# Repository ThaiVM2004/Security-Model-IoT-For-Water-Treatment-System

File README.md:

# 🔒 Security Model IoT for Water Treatment System

A multi-layered IoT security system for real-time water treatment monitoring and control. The project integrates embedded sensors, a network firewall, cloud services, and a web dashboard with role-based access control (RBAC) to securely supervise water quality across collection and discharge tanks.

---

## 📋 Table of Contents

- [Overview](#overview)
- [System Architecture](#system-architecture)
- [Hardware Components](#hardware-components)
- [Software Stack](#software-stack)
- [Repository Structure](#repository-structure)
- [Getting Started](#getting-started)
  - [STM32 Firmware](#stm32-firmware)
  - [ESP32 Firmware](#esp32-firmware)
  - [Raspberry Pi Gateway](#raspberry-pi-gateway)
  - [Web Application](#web-application)
- [Security Features](#security-features)
- [Sensors & Measurements](#sensors--measurements)
- [Communication Protocols](#communication-protocols)
- [License](#license)

---

## Overview

This system monitors and controls a water treatment facility through four interconnected layers:

| Layer | Hardware | Role |
|-------|----------|------|
| **Sensor** | STM32F1 + Sensors | Reads temperature, water level, TDS, and pH |
| **Gateway** | ESP32 | Bridges UART sensor data to MQTT over WiFi |
| **Edge Server** | Raspberry Pi | Runs a kernel-level firewall, syncs data to Firebase, and enforces RBAC for commands |
| **Dashboard** | Browser (React) | Provides real-time monitoring, alerting, and device control |

---

## System Architecture

```
┌──────────────┐   UART    ┌──────────────┐   MQTT    ┌─────────────────────────┐
│  STM32F1     │ ────────► │  ESP32       │ ────────► │  Raspberry Pi           │
│  (Sensors +  │ ◄──────── │  (WiFi/MQTT  │ ◄──────── │  ┌─────────────────┐    │
│   Actuators) │  Commands │   Gateway)   │  Control  │  │ Kernel Firewall │    │
└──────────────┘           └──────────────┘           │  └─────────────────┘    │
                                                      │  ┌─────────────────┐    │
                                                      │  │ firebase_rt.py  │───►│ Firebase
                                                      │  │ (Sensor → DB)   │    │ (Realtime DB
                                                      │  └─────────────────┘    │  + Firestore
                                                      │  ┌─────────────────┐    │  + Auth)
                                                      │  │ parse_new_ver.py│◄───│
                                                      │  │ (RBAC Commands) │    │
                                                      │  └─────────────────┘    │
                                                      │  ┌─────────────────┐    │
                                                      │  │ get-info.py     │◄───│
                                                      │  │ (User Sync)     │    │
                                                      │  └─────────────────┘    │
                                                      └─────────────────────────┘
                                                                 ▲
                                                                 │ HTTP / Firebase SDK
                                                                 ▼
                                                      ┌─────────────────────────┐
                                                      │  React Web Dashboard    │
                                                      │  + Node.js Backend      │
                                                      │  (Admin / User1 / User2)│
                                                      └─────────────────────────┘
```

---

## Hardware Components

| Component | Model | Purpose |
|-----------|-------|---------|
| Microcontroller | STM32F103 | Sensor acquisition & actuator control via FreeRTOS |
| WiFi/MQTT Gateway | ESP32 | Bridges UART ↔ MQTT over WiFi |
| Edge Server | Raspberry Pi (64-bit) | Runs firewall, Python scripts, MQTT broker |
| Temperature Sensor | DS18B20 | 1-Wire digital thermometer (−55 °C to +125 °C) |
| Water Level Sensor | HC-SR04 | Ultrasonic distance → water level percentage |
| TDS Sensor | Analog probe | Total Dissolved Solids / turbidity measurement |
| pH Sensor | Analog electrode | pH 0–14, two-point calibration (pH 4.0 & 9.0) |
| Actuators | Pumps, valves, fans, bulbs | 8 controllable devices (4 per treatment unit) |

---

## Software Stack

| Layer | Technologies |
|-------|-------------|
| STM32 Firmware | C, STM32 HAL, FreeRTOS (CMSIS-OS), ADC, UART, Timers |
| ESP32 Firmware | Arduino (C++), WiFi, PubSubClient (MQTT), ArduinoJson |
| Linux / Gateway | Python 3, paho-mqtt, firebase-admin SDK, SQLite 3, Bash |
| Kernel Security | C, Linux Netfilter framework, kernel module (`.ko`) |
| Frontend | React 19, React Router 7, Firebase JS SDK, Recharts, Tabler Icons, Lucide |
| Backend | Node.js, Express.js, Axios, CORS |
| Cloud | Firebase Authentication, Firestore, Realtime Database |
| PCB Design | KiCad (schematic + PCB layout) |

---

## Repository Structure

```
├── Circuit/
│   ├── main_circuit.kicad_sch      # KiCad schematic
│   ├── main_pcb.kicad_pcb          # KiCad PCB layout
│   └── fab.zip                     # Fabrication files
│
├── Source/
│   ├── STM32 Code/
│   │   ├── Config/main.ioc         # STM32CubeMX project file
│   │   ├── Inc/                    # Header files (main.h, sensor headers, FreeRTOS config)
│   │   └── Src/
│   │       ├── main.c              # Core: FreeRTOS tasks, UART, device control
│   │       ├── pH.c                # pH sensor driver (two-point calibration)
│   │       ├── temp.c              # DS18B20 temperature driver (1-Wire via UART)
│   │       ├── turbidity.c         # TDS/turbidity driver (ADC + polynomial)
│   │       ├── water_level.c       # HC-SR04 ultrasonic driver (timer capture)
│   │       └── freertos.c          # FreeRTOS kernel configuration
│   │
│   ├── ESP32 Code/
│   │   └── main/main.ino           # WiFi + MQTT gateway, UART ↔ JSON bridge
│   │
│   ├── Linux/
│   │   ├── Kernel Module/
│   │   │   ├── nf_kernel.c         # Netfilter firewall (whitelist ports)
│   │   │   └── Makefile            # Kernel module build for Raspberry Pi
│   │   └── Script/
│   │       ├── firebase_rt.py      # MQTT subscriber → Firebase Realtime DB
│   │       ├── get-info.py         # Firestore → SQLite user sync
│   │       ├── parse_new_ver.py    # RBAC command processor (Firestore → MQTT)
│   │       └── run_process.sh      # Process orchestrator
│   │
│   └── Web Code/
│       └── superviso-ui/
│           ├── backend/server.js   # Express.js proxy to Raspberry Pi
│           ├── src/
│           │   ├── App.js          # React router & layout
│           │   ├── LoginForm/      # Firebase authentication UI
│           │   ├── Register/       # User registration with role selection
│           │   ├── Admin/          # Admin dashboard (system health + alerts)
│           │   └── Dashboard/      # User dashboards (sensor data + device control)
│           └── package.json
│
└── README.md
```

---

## Getting Started

### Prerequisites

- **STM32:** STM32CubeIDE or compatible ARM toolchain
- **ESP32:** Arduino IDE with ESP32 board package
- **Raspberry Pi:** Raspberry Pi OS (64-bit), Python 3, Mosquitto MQTT broker
- **Web:** Node.js ≥ 18, npm
- **Cloud:** Firebase project with Authentication, Firestore, and Realtime Database enabled

### STM32 Firmware

1. Open `Source/STM32 Code/Config/main.ioc` in STM32CubeMX to review pin configuration.
2. Build the project with STM32CubeIDE using the files in `Src/` and `Inc/`.
3. Flash the firmware to the STM32F103 board.

### ESP32 Firmware

1. Open `Source/ESP32 Code/main/main.ino` in Arduino IDE.
2. Install required libraries: **PubSubClient**, **ArduinoJson**, **WiFi**.
3. Update WiFi SSID/password and MQTT broker IP in the sketch.
4. Upload to the ESP32 board.

### Raspberry Pi Gateway

```bash
# Install system dependencies
sudo apt update && sudo apt install -y mosquitto mosquitto-clients python3-pip

# Install Python packages
pip3 install paho-mqtt firebase-admin

# Build and load the kernel firewall module
cd Source/Linux/Kernel\ Module
make
sudo insmod nf_kernel.ko

# Start the data pipeline
cd ../Script
bash run_process.sh
```

### Web Application

```bash
cd Source/Web\ Code/superviso-ui

# Install dependencies
npm install

# Start the backend proxy
cd backend && node server.js &

# Start the React development server
cd .. && npm start
```

The dashboard will be available at `http://localhost:3000`.

---

## Security Features

| Feature | Implementation | Layer |
|---------|---------------|-------|
| **Network Firewall** | Linux kernel Netfilter module with port whitelist (22, 53, 443, 1883, 67/68) | Kernel |
| **Default-Deny Policy** | Only whitelisted ports and established TCP connections are accepted | Kernel |
| **Authentication** | Firebase Authentication (email/password) | Cloud / Web |
| **Role-Based Access Control** | Admin, User1, User2 roles verified against SQLite DB before command execution | Edge Server |
| **Command Verification** | Commands parsed and validated (`db/user/role/device/action`) before MQTT dispatch | Edge Server |
| **Audit Trail** | Processed flags, timestamps, and error messages stored in Firestore | Cloud |
| **Firewall Logging** | All accepted/dropped packets logged via kernel `pr_info()` | Kernel |

---

## Sensors & Measurements

| Sensor | Parameter | Range | Technique |
|--------|-----------|-------|-----------|
| DS18B20 | Temperature | −55 °C to +125 °C | 1-Wire protocol via UART half-duplex |
| HC-SR04 | Water Level | 0–100 % (1–12.5 cm distance) | Ultrasonic time-of-flight, timer input capture |
| TDS Probe | Turbidity | 0–1000+ ppm | ADC median filter + polynomial compensation |
| pH Electrode | pH | 0–14 | ADC with two-point calibration (pH 4.0 / 9.0) |

Alert thresholds (QCVN 40:2011 — Vietnamese water quality standard):

- **pH:** 6.5–8.5
- **Temperature:** 15–35 °C
- **Turbidity:** Warning at 250 ppm, Critical at 350 ppm
- **Water Level:** 30–80 %

---

## Communication Protocols

| Protocol | Usage | Details |
|----------|-------|---------|
| UART | STM32 ↔ ESP32 | 115200 baud (commands), 9600 baud (sensor data) |
| MQTT | ESP32 ↔ Broker ↔ RPi | Topics: `iot/sensor1`, `iot/sensor2`, `iot/control` |
| 1-Wire | STM32 ↔ DS18B20 | Temperature reads via UART half-duplex |
| ADC | STM32 ↔ TDS/pH | Analog sampling with median filter |
| HTTP | Web ↔ Backend ↔ RPi | Express.js proxy for registration notifications |
| WebSocket | Web ↔ Firebase | Real-time sensor data via Firebase Realtime DB |

---

## License

This project is developed for academic and research purposes.

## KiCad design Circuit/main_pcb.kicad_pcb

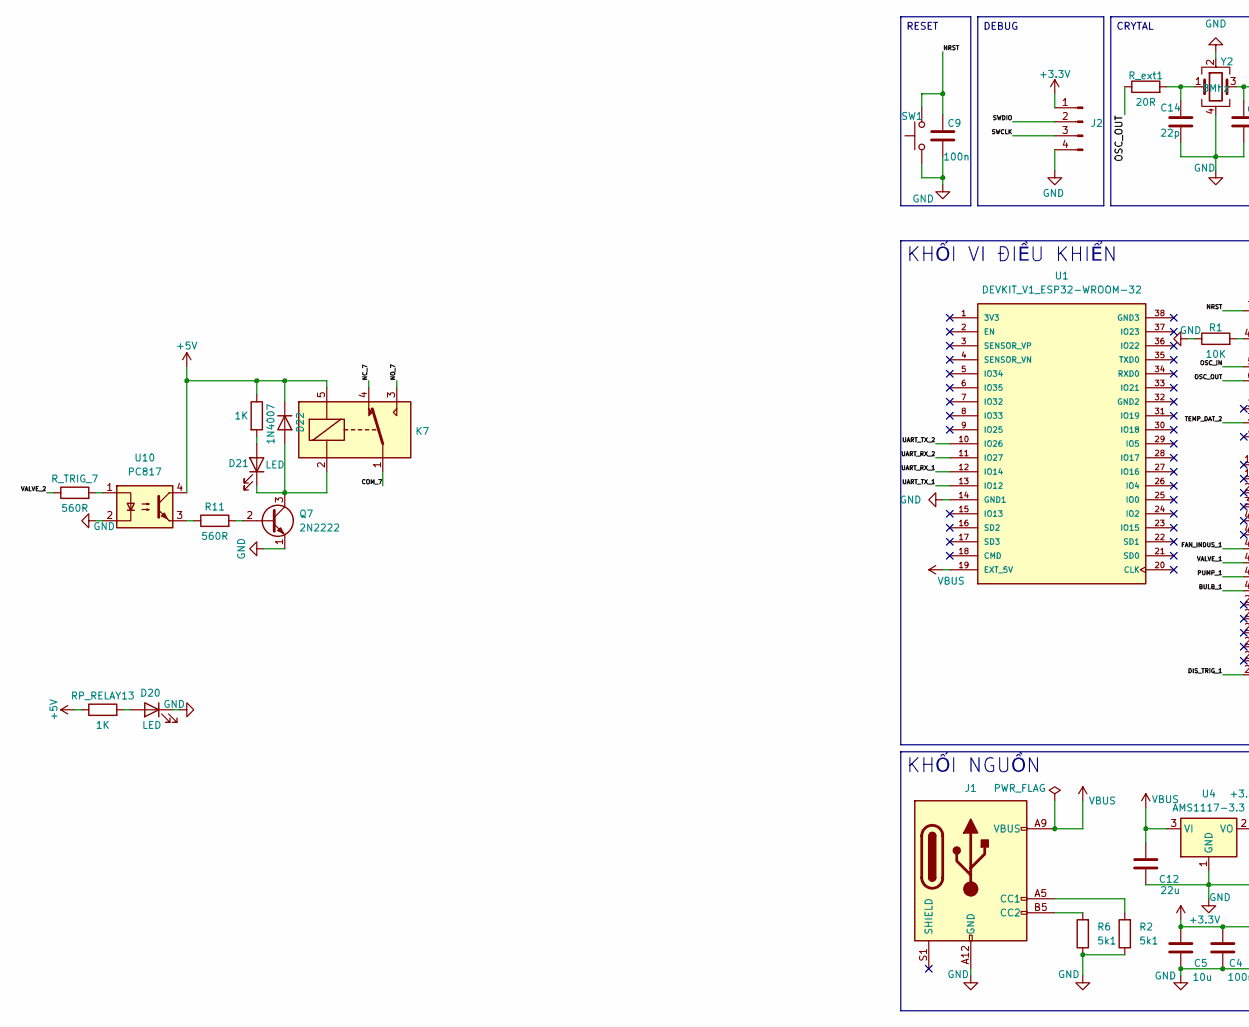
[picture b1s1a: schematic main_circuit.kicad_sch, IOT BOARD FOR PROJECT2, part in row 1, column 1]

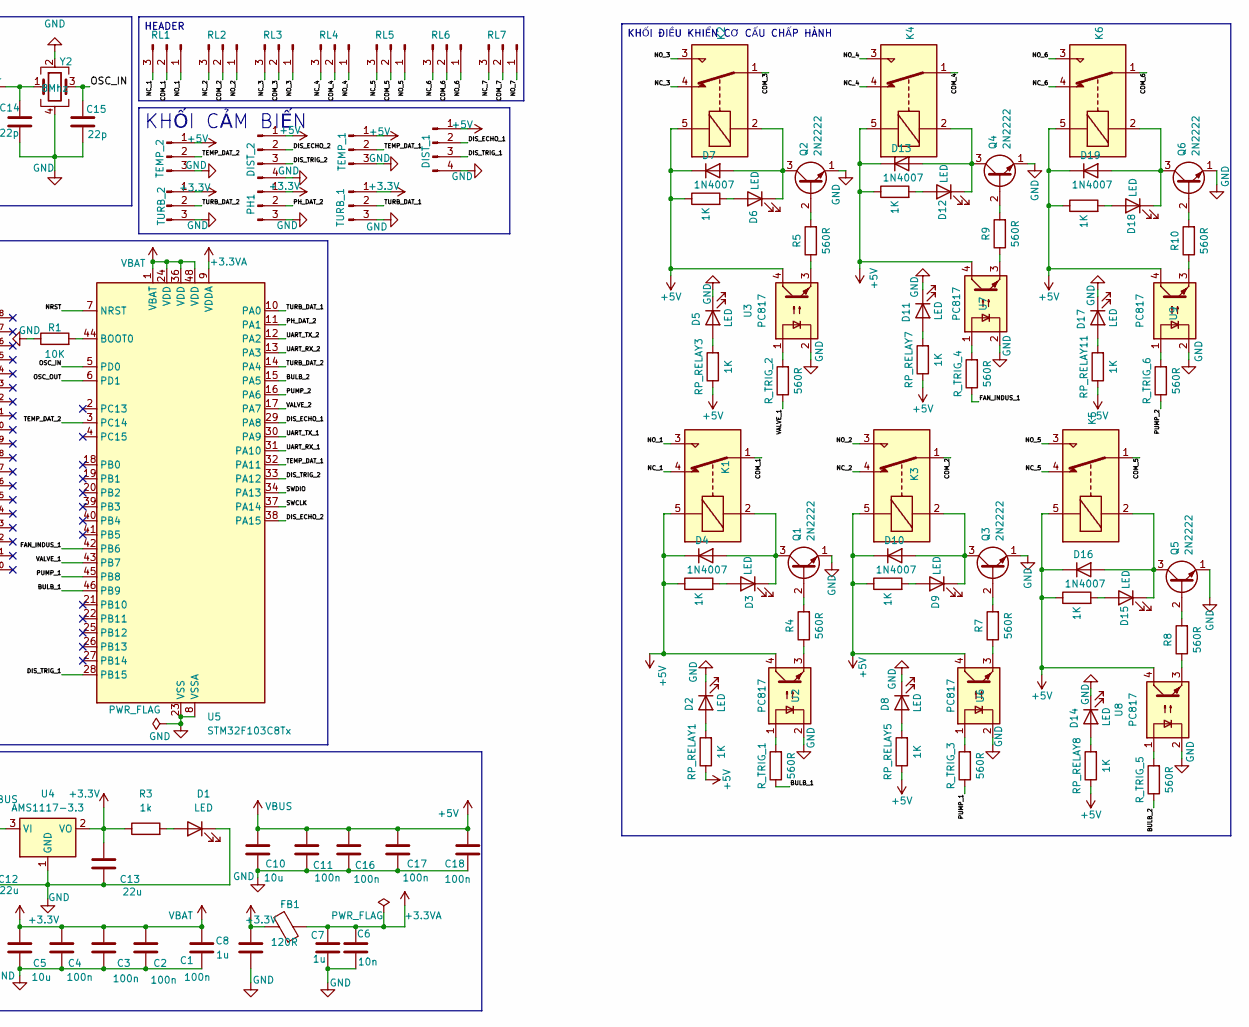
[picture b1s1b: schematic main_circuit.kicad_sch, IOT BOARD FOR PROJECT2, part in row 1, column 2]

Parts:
C1, C2, C3, C4, C9, C11, C16, C17, C18: 100n; C_0805_2012Metric
C5, C10: 10u; C_0805_2012Metric
C6: 10n; C_0805_2012Metric
C7, C8: 1u; C_0805_2012Metric
C12, C13: 22u; C_0805_2012Metric
C14, C15: 22p; C_0603_1608Metric
D1, D2, D3, D5, D6, D8, D9, D11, D12, D14, D15, D17, D18, D20, D21: LED; LED_0805_2012Metric
D4, D7, D10, D13, D16, D19, D22: 1N4007; D_DO-41_SOD81_P10.16mm_Horizontal
DIST_1, DIST_2: Conn_01x04_Pin; PinHeader_1x04_P2.54mm_Vertical
FB1: 120R; L_0805_2012Metric
J1: USB_C_Receptacle_PowerOnly_6P; USB_C_Receptacle_GCT_USB4125-xx-x_6P_TopMnt_Horizontal
J2: ST-LINK; PinHeader_1x04_P2.54mm_Vertical
K1, K2, K3, K4, K5, K6, K7: SANYOU_SRD_Form_C; Relay_SPDT_SANYOU_SRD_Series_Form_C
PH1: Conn_01x03_Pin; PinHeader_1x03_P2.54mm_Vertical
Q1, Q2, Q3, Q4, Q5, Q6, Q7: 2N2222; PinHeader_1x03_P1.27mm_Vertical
R1: 10K; R_0805_2012Metric
R2, R6: 5k1; R_0805_2012Metric
R3: 1k; R_0805_2012Metric
R4, R5, R7, R8, R9, R10, R11: 560R; R_0805_2012Metric
RL1, RL2, RL3, RL4, RL5, RL6, RL7: Conn_01x03_Pin; PinHeader_1x03_P2.54mm_Vertical
RP_RELAY1, RP_RELAY2, RP_RELAY3, RP_RELAY4, RP_RELAY5, RP_RELAY6, RP_RELAY7, RP_RELAY8, RP_RELAY9, RP_RELAY10, RP_RELAY11, RP_RELAY12, RP_RELAY13, RP_RELAY14: 1K; R_0805_2012Metric
R_TRIG_1, R_TRIG_2, R_TRIG_3, R_TRIG_4, R_TRIG_5, R_TRIG_6, R_TRIG_7: 560R; R_0805_2012Metric
R_ext1: 20R; R_0805_2012Metric
SW1: SW_Push; SW_SPST_PTS647_Sx70
TEMP_1, TEMP_2: Conn_01x03_Pin; PinHeader_1x03_P2.54mm_Vertical
TURB_1, TURB_2: Conn_01x03_Pin; PinHeader_1x03_P2.54mm_Vertical
U1: DEVKIT_V1_ESP32-WROOM-32; MODULE_DEVKIT_V1_ESP32-WROOM-32; PARTREV N/A
U2, U3, U6, U7, U8, U9, U10: PC817; DIP-4_W7.62mm
U4: AMS1117-3.3; SOT-223-3_TabPin2
U5: STM32F103C8Tx; LQFP-48_7x7mm_P0.5mm
Y2: 8Mhz; Crystal_SMD_5032-4Pin_5.0x3.2mm

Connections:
+3.3V: C1.1, C2.1, C3.1, C4.1, C5.1, C8.1, C13.1, FB1.2, J2.1, PH1.1, R3.1, TURB_1.1, TURB_2.1, U4.2 (VO), U5.1 (VBAT), U5.24 (VDD), U5.36 (VDD), U5.48 (VDD)
+3.3VA: C6.1, C7.1, FB1.1, U5.9 (VDDA)
+5V: C10.1, C11.1, C12.1, C16.1, C17.1, C18.1, D4.1 (K), D7.1 (K), D10.1 (K), D13.1 (K), D16.1 (K), D19.1 (K), D22.1 (K), DIST_1.1, DIST_2.1, J1.A9 (VBUS), J1.B9 (VBUS), K1.5, K2.5, K3.5, K4.5, K5.5, K6.5, K7.5, RP_RELAY1.1, RP_RELAY2.1, RP_RELAY3.1, RP_RELAY4.1, RP_RELAY5.1, RP_RELAY6.1, RP_RELAY7.1, RP_RELAY8.1, RP_RELAY9.1, RP_RELAY10.1, RP_RELAY11.1, RP_RELAY12.1, RP_RELAY13.1, RP_RELAY14.1, TEMP_1.1, TEMP_2.1, U1.19 (EXT_5V), U2.4, U3.4, U4.3 (VI), U6.4, U7.4, U8.4, U9.4, U10.4
/BULB_1: R_TRIG_1.1, U5.46 (PB9)
/BULB_2: R_TRIG_5.1, U5.15 (PA5)
/COM_1: K1.1, RL1.2
/COM_2: K3.1, RL2.2
/COM_3: K2.1, RL3.2
/COM_4: K4.1, RL4.2
/COM_5: K5.1, RL5.2
/COM_6: K6.1, RL6.2
/COM_7: K7.1, RL7.2
/DIS_ECHO_1: DIST_1.2, U5.29 (PA8)
/DIS_ECHO_2: DIST_2.2, U5.38 (PA15)
/DIS_TRIG_1: DIST_1.3, U5.28 (PB15)
/DIS_TRIG_2: DIST_2.3, U5.33 (PA12)
/FAN_INDUS_1: R_TRIG_4.1, U5.42 (PB6)
/NC_1: K1.4, RL1.3
/NC_2: K3.4, RL2.3
/NC_3: K2.4, RL3.3
/NC_4: K4.4, RL4.3
/NC_5: K5.4, RL5.3
/NC_6: K6.4, RL6.3
/NC_7: K7.4, RL7.3
/NO_1: K1.3, RL1.1
/NO_2: K3.3, RL2.1
/NO_3: K2.3, RL3.1
/NO_4: K4.3, RL4.1
/NO_5: K5.3, RL5.1
/NO_6: K6.3, RL6.1
/NO_7: K7.3, RL7.1
/NRST: C9.1, SW1.2, U5.7 (NRST)
/OSC_IN: C15.1, U5.5 (PD0), Y2.3
/OSC_OUT: R_ext1.1, U5.6 (PD1)
/PH_DAT_2: PH1.2, U5.11 (PA1)
/PUMP_1: R_TRIG_3.1, U5.45 (PB8)
/PUMP_2: R_TRIG_6.1, U5.16 (PA6)
/SWCLK: J2.3, U5.37 (PA14)
/SWDIO: J2.2, U5.34 (PA13)
/TEMP_DAT_1: TEMP_1.2, U5.32 (PA11)
/TEMP_DAT_2: TEMP_2.2, U5.3 (PC14)
/TURB_DAT_1: TURB_1.2, U5.10 (PA0)
/TURB_DAT_2: TURB_2.2, U5.14 (PA4)
/UART_RX_1: U1.12 (IO14), U5.31 (PA10)
/UART_RX_2: U1.11 (IO27), U5.13 (PA3)
/UART_TX_1: U1.13 (IO12), U5.30 (PA9)
/UART_TX_2: U1.10 (IO26), U5.12 (PA2)
/VALVE_1: R_TRIG_2.1, U5.43 (PB7)
/VALVE_2: R_TRIG_7.1, U5.17 (PA7)
GND: C1.2, C2.2, C3.2, C4.2, C5.2, C6.2, C7.2, C8.2, C9.2, C10.2, C11.2, C12.2, C13.2, C14.2, C15.2, C16.2, C17.2, C18.2, D1.1 (K), D2.1 (K), D5.1 (K), D8.1 (K), D11.1 (K), D14.1 (K), D17.1 (K), D20.1 (K), DIST_1.4, DIST_2.4, J1.A12 (GND), J1.B12 (GND), J2.4, PH1.3, Q1.1 (E), Q2.1 (E), Q3.1 (E), Q4.1 (E), Q5.1 (E), Q6.1 (E), Q7.1 (E), R1.1, R2.1, R6.1, SW1.1, TEMP_1.3, TEMP_2.3, TURB_1.3, TURB_2.3, U1.14 (GND1), U2.2, U3.2, U4.1 (GND), U5.8 (VSSA), U5.23 (VSS), U5.35 (VSS), U5.47 (VSS), U6.2, U7.2, U8.2, U9.2, U10.2, Y2.2, Y2.4
unnamed: C14.1, R_ext1.2, Y2.1
unnamed: D1.2 (A), R3.2
unnamed: D2.2 (A), RP_RELAY1.2
unnamed: D3.2 (A), RP_RELAY2.2
unnamed: D3.1 (K), D4.2 (A), K1.2, Q1.3 (C)
unnamed: D5.2 (A), RP_RELAY3.2
unnamed: D6.2 (A), RP_RELAY4.2
unnamed: D6.1 (K), D7.2 (A), K2.2, Q2.3 (C)
unnamed: D8.2 (A), RP_RELAY5.2
unnamed: D9.2 (A), RP_RELAY6.2
unnamed: D9.1 (K), D10.2 (A), K3.2, Q3.3 (C)
unnamed: D11.2 (A), RP_RELAY7.2
unnamed: D12.2 (A), RP_RELAY10.2
unnamed: D12.1 (K), D13.2 (A), K4.2, Q4.3 (C)
unnamed: D14.2 (A), RP_RELAY8.2
unnamed: D15.2 (A), RP_RELAY9.2
unnamed: D15.1 (K), D16.2 (A), K5.2, Q5.3 (C)
unnamed: D17.2 (A), RP_RELAY11.2
unnamed: D18.2 (A), RP_RELAY12.2
unnamed: D18.1 (K), D19.2 (A), K6.2, Q6.3 (C)
unnamed: D20.2 (A), RP_RELAY13.2
unnamed: D21.2 (A), RP_RELAY14.2
unnamed: D21.1 (K), D22.2 (A), K7.2, Q7.3 (C)
unnamed: J1.A5 (CC1), R2.2
unnamed: J1.B5 (CC2), R6.2
unnamed: Q1.2 (B), R4.2
unnamed: Q2.2 (B), R5.2
unnamed: Q3.2 (B), R7.2
unnamed: Q4.2 (B), R9.2
unnamed: Q5.2 (B), R8.2
unnamed: Q6.2 (B), R10.2
unnamed: Q7.2 (B), R11.2
unnamed: R4.1, U2.3
unnamed: R5.1, U3.3
unnamed: R7.1, U6.3
unnamed: R8.1, U8.3
unnamed: R9.1, U7.3
unnamed: R10.1, U9.3
unnamed: R11.1, U10.3
unnamed: R_TRIG_1.2, U2.1
unnamed: R_TRIG_2.2, U3.1
unnamed: R_TRIG_3.2, U6.1
unnamed: R_TRIG_4.2, U7.1
unnamed: R_TRIG_5.2, U8.1
unnamed: R_TRIG_6.2, U9.1
unnamed: R_TRIG_7.2, U10.1
unnamed: R1.2, U5.44 (BOOT0)

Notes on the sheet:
KHỐI ĐIỀU KHIỂN CƠ CẤU CHẤP HÀNH
KHỐI CẢM BIẾN
DEBUG
HEADER
KHỐI NGUỒN
CRYTAL
KHỐI VI ĐIỀU KHIỂN
RESET

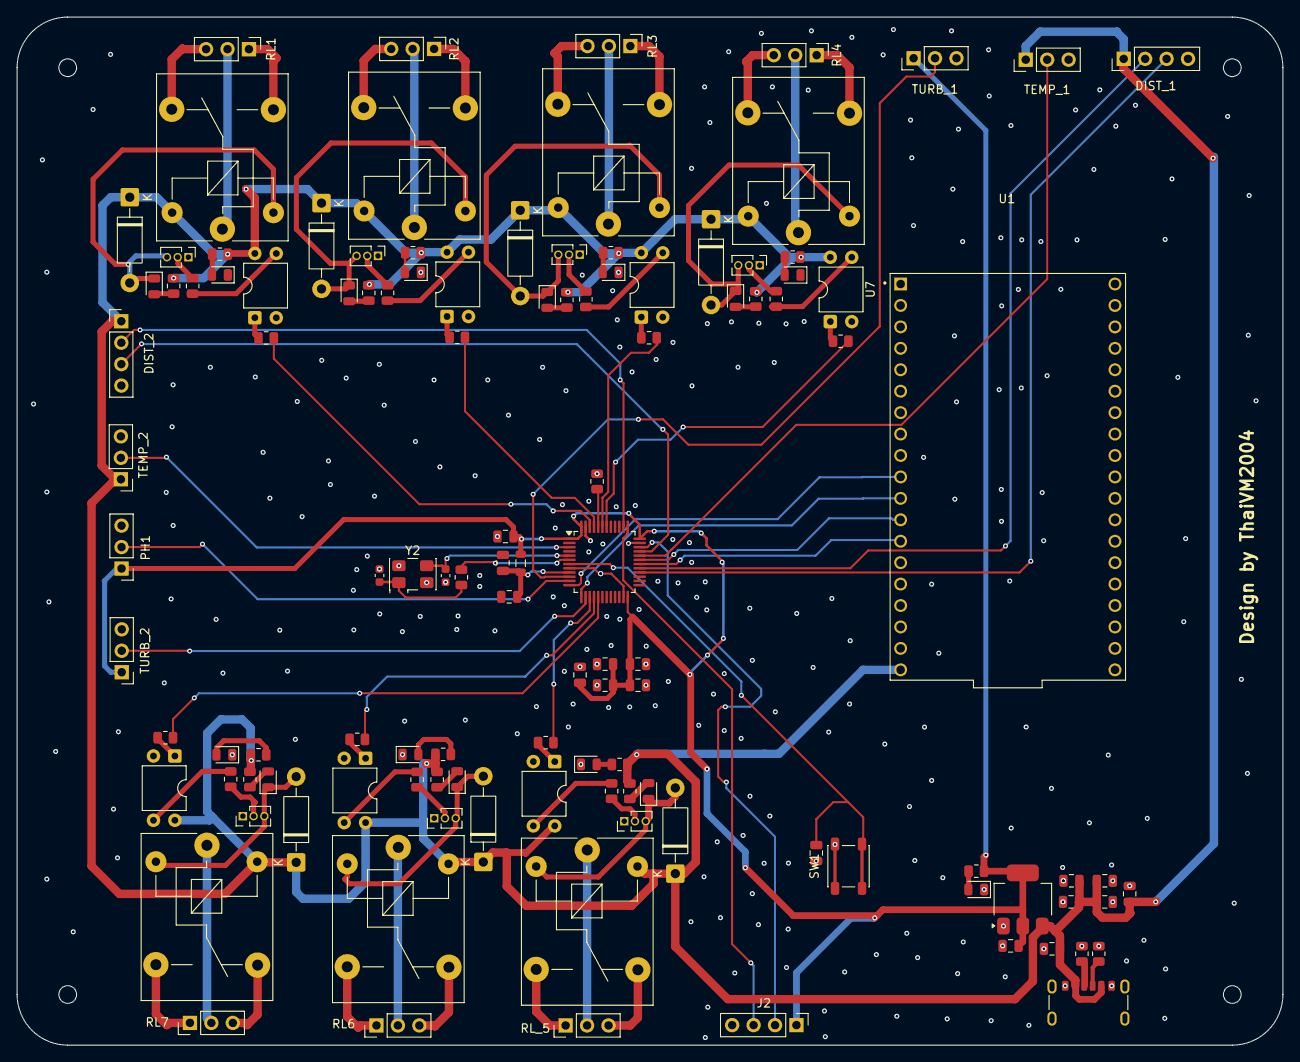
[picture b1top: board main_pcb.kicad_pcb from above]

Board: 2 copper layers, 150.0 x 121.8 mm, 120 parts (0 on the bottom side), 97 nets.

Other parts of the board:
H1, H2, H3, H4: MountingHole; MountingHole_2.1mm

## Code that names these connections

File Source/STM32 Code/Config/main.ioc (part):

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Mcu.Name=STM32F103C(8-B)Tx
Mcu.Package=LQFP48
Mcu.UserName=STM32F103C8Tx
PA0-WKUP.Signal=ADCx_IN0
PA1.Signal=ADCx_IN1
PA10.Mode=Asynchronous
PA10.Signal=USART1_RX
PA11.Signal=GPIO_Output
PA12.Signal=GPIO_Output
PA15.Signal=S_TIM2_CH1_ETR
PA2.Mode=Asynchronous
PA2.Signal=USART2_TX
PA3.Mode=Asynchronous
PA3.Signal=USART2_RX
PA4.Signal=ADCx_IN4
PA5.Signal=GPIO_Output
PA6.Signal=GPIO_Output
PA7.Signal=GPIO_Output
PA8.Signal=S_TIM1_CH1
PA9.Mode=Asynchronous
PA9.Signal=USART1_TX
PB0.Signal=GPIO_Output
PB15.Signal=GPIO_Output
PB6.Signal=GPIO_Output
PB7.Signal=GPIO_Output
PB8.Signal=GPIO_Output
PB9.Signal=GPIO_Output
PC13-TAMPER-RTC.Signal=GPIO_Output
PC14-OSC32_IN.Signal=GPIO_Output
PD0-OSC_IN.Mode=HSE-External-Oscillator
PD0-OSC_IN.Signal=RCC_OSC_IN
PD1-OSC_OUT.Mode=HSE-External-Oscillator
PD1-OSC_OUT.Signal=RCC_OSC_OUT
RCC.SYSCLKFreq_VALUE=72000000
RCC.SYSCLKSource=RCC_SYSCLKSOURCE_PLLCLK
board=custom

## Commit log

2026-02-05 Revise project title and add project description
    Updated project title and added a brief description.
2026-04-08 Write comprehensive README.md with full project documentation
    Agent-Logs-Url: https://github.com/ThaiVM2004/Security-Model-IoT-For-Water-Treatment-System/sessions/c67cd56f-4304-4802-95be-8a3698b37a1b
